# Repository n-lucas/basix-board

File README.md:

# BASIX Board

Open hardware embedded I/O controller for automation and IoT projects.

## Overview

BASIX is an open hardware embedded controller built primarily with through-hole (THT) components and based on the PIC18F46K20 microcontroller, providing Ethernet, RS485 and other peripherals.

It was designed as an educational platform for learning embedded electronics, prototyping automation systems, and experimenting with industrial communication interfaces and isolated I/O.

The complete hardware design is publicly available, including schematics, PCB layouts, manufacturing files, and documentation.

## Features

- 12VDC power input
- PIC18F46K20 microcontroller (16 MHz)
- Ethernet interface (W5500)
- RS-485 interface
- Real-Time Clock (RTC) with backup battery
- External 128 KB SPI EEPROM
- 4× optically isolated digital inputs
- 2× analog inputs (0–10 V)
- 2× relay outputs
- 2× digital/PWM outputs
- 5-position DIP switch for configuration
- 3x General purpose LEDs (feedback, status, etc)
- ICSP programming header

## Fabrication / Assembly

BASIX was designed with simplicity and accessibility in mind. The board uses mostly through-hole (THT) components, allowing it to be assembled using a standard soldering iron without requiring specialized equipment such as a reflow oven or hot-air station.

The PCB can be manufactured by any standard PCB fabrication service using the Gerber files available in the `hardware/gerbers` directory.

This approach makes the project suitable for hobbyists, students, makers, and anyone interested in learning embedded hardware design or building their own automation controller.

## Repository Structure

| Directory | Description |
|---|---|
| `hardware/kicad/` | Editable KiCad project files, including schematics, PCB layout, symbols, and footprints. |
| `hardware/gerbers/` | Gerber and drill files ready for PCB manufacturing. |
| `hardware/bom/` | Bill of Materials (BOM), including component references, quantities, and part numbers. |
| `docs/` | Technical documentation, hardware architecture, schematics, design notes, and revision history. |
| `images/` | Board photographs, KiCad 3D renders, diagrams, and images used throughout the documentation. |

## Documentation

Additional documentation can be found in the `docs` directory.

Topics include:

- Hardware architecture
- Design decisions
- Revision history

## Expansion Modules

BASIX was designed to be easily expanded through its RS-485 interface.

Developers, students, and makers are encouraged to design and share their own expansion modules, such as:

- Remote digital I/O
- Analog input/output modules
- Relay expansion boards
- Environmental sensors
- Energy monitoring
- LCD/HMI interfaces
- Motor controllers
- Industrial protocol gateways

The goal is to build an open ecosystem of interoperable modules that can communicate with BASIX using a simple RS-485 network.

If you develop an expansion board, feel free to share your project with the community by opening a Pull Request or creating your own repository referencing BASIX.

## Project Status

**Current release**

- Hardware Revision C
- Prototype validated

**Planned**

- Open-source firmware
- Desktop application (Lazarus) for monitoring and controlling I/O

## License

This project is licensed under the CERN Open Hardware Licence Version 2 - Weakly Reciprocal (CERN-OHL-W v2).

See the `LICENSE` file for details.

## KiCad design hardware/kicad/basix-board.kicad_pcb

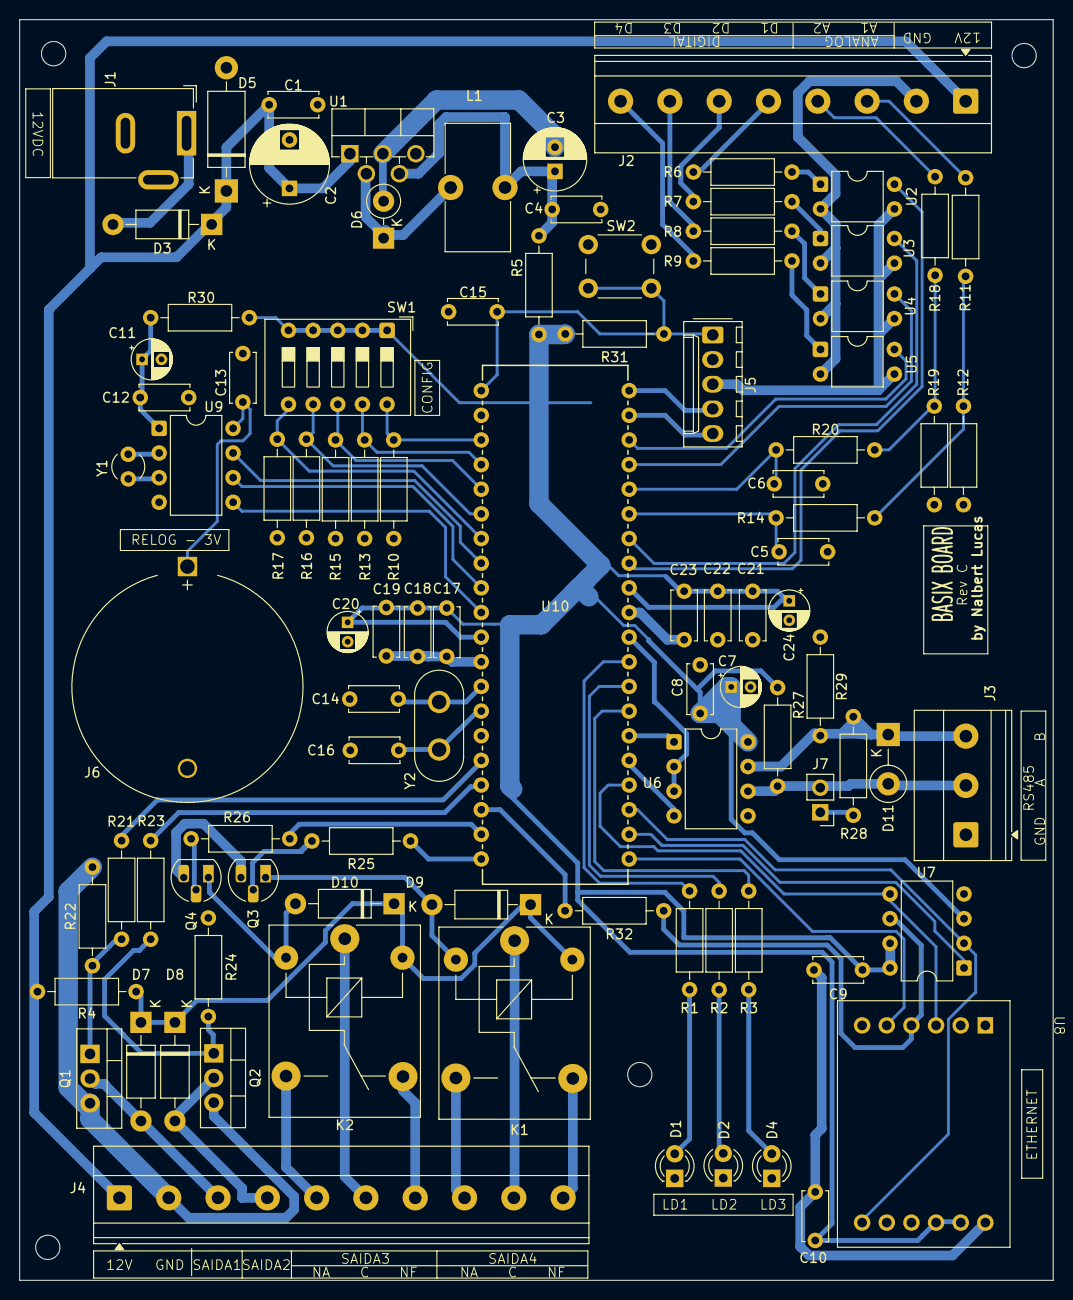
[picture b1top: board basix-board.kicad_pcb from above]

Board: 2 copper layers, 106.5 x 129.9 mm, 95 parts (0 on the bottom side), 78 nets.

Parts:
C1, C4, C5, C6, C8, C9, C10, C12, C13, C14, C15, C16, C17, C18, C19, C21, C22, C23: 100nF; C_Disc_D5.0mm_W2.5mm_P5.00mm
C2: 680uF; CP_Radial_D8.0mm_P5.00mm
C3: 220uF; CP_Radial_D6.3mm_P2.50mm
C7, C11, C20, C24: 10uF; CP_Radial_D4.0mm_P2.00mm
D1, D2, D4: LED; LED_D3.0mm
D3, D7, D8, D9, D10: 1N4007; D_DO-41_SOD81_P10.16mm_Horizontal
D5: P6KE68A; D_DO-15_P12.70mm_Horizontal
D6: 1N5819; D_DO-41_SOD81_P3.81mm_Vertical_KathodeUp
D11: P6KE15CA; D_DO-15_P5.08mm_Vertical_KathodeUp
J1: Barrel Connector; BarrelJack_GCT_DCJ200-10-A_Horizontal
J2: Conn_01x08_Pin; TerminalBlock_Phoenix_MKDS-1,5-8-5.08_1x08_P5.08mm_Horizont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
J3: Conn_01x03_Pin; TerminalBlock_Phoenix_MKDS-1,5-3-5.08_1x03_P5.08mm_Horizont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
J4: Conn_01x10_Pin; TerminalBlock_Phoenix_MKDS-1,5-10-5.08_1x10_P5.08mm_Horizon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
J5: KK Connector; Molex_KK-254_AE-6410-05A_1x05_P2.54mm_Vertical
J6: BAT Connector; BatteryHolder_MYOUNG_BS-07-A1BJ001_CR2032
J7: Conn_01x02_Pin; PinHeader_1x02_P2.54mm_Vertical
K1, K2: SPDT 12V; Relay_SPDT_SANYOU_SRD_Series_Form_C
L1: 33uH; L_Toroid_Vertical_L13.0mm_W6.5mm_P5.60mm
Q1, Q2: IRLZ44N; TO-220-3_Vertical
Q3, Q4: BC548; TO-92_HandSolder
R1, R2, R3: 220R; R_Axial_DIN0207_L6.3mm_D2.5mm_P10.16mm_Horizontal
R4, R5: 0R; R_Axial_DIN0207_L6.3mm_D2.5mm_P10.16mm_Horizontal
R6, R7, R8, R9, R25, R26: 2k2; R_Axial_DIN0207_L6.3mm_D2.5mm_P10.16mm_Horizontal
R10, R12, R13, R15, R16, R17, R19, R31: 10k; R_Axial_DIN0207_L6.3mm_D2.5mm_P10.16mm_Horizontal
R11, R18: 20k; R_Axial_DIN0207_L6.3mm_D2.5mm_P10.16mm_Horizontal
R14, R20: 1k; R_Axial_DIN0207_L6.3mm_D2.5mm_P10.16mm_Horizontal
R21, R23: 100R; R_Axial_DIN0207_L6.3mm_D2.5mm_P10.16mm_Horizontal
R22, R24: 100k; R_Axial_DIN0207_L6.3mm_D2.5mm_P10.16mm_Horizontal
R27, R29: 4k7; R_Axial_DIN0207_L6.3mm_D2.5mm_P10.16mm_Horizontal
R28: 120R; R_Axial_DIN0207_L6.3mm_D2.5mm_P10.16mm_Horizontal
R30: 10R; R_Axial_DIN0207_L6.3mm_D2.5mm_P10.16mm_Horizontal
R32: 33R; R_Axial_DIN0207_L6.3mm_D2.5mm_P10.16mm_Horizontal
SW1: DIP Switch; SW_DIP_SPSTx05_Slide_9.78x14.88mm_W7.62mm_P2.54mm
SW2: SW_Push; SW_PUSH_6mm
U1: LM2596T-3.3; TO-220F-5_P3.4x2.06mm_StaggerEven_Lead1.86mm_Vertical
U2, U3, U4, U5: PC817; DIP-4_W7.62mm
U6: MAX485; DIP-8_W7.62mm
U7: 25LC1024; DIP-8_W7.62mm
U8: W5500 Lite; W5500_Lite_2x6_2.54mm_20.32mm
U9: DS1302+; DIP-8_W7.62mm
U10: pic18f46k20-i/p; PDIP40_600MC_MCH
Y1: Crystal; Crystal_AT310_D3.0mm_L10.0mm_Vertical
Y2: Crystal; Crystal_HC50_Vertical

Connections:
3.3V: C7.1, C8.1, C9.1, C10.1, C17.1, C18.1, C19.1, C20.1, C21.1, C22.1, C23.1, C24.1, J5.2, R5.1, R27.2, R30.1, R31.2, SW1.1, SW1.2, SW1.3, SW1.4, SW1.5, U6.8 (VCC), U7.3 (~WP), U7.7 (~HOLD), U7.8 (VCC), U8.8 (VIN), U8.9 (VIN), U10.11 (VDD), U10.32 (VDD)
12VDC: C1.1, C2.1, D3.1 (K), D5.1 (A1), J2.1, J4.1, R4.1, U1.1 (VIN)
12VDC_IN: D3.2 (A), J1.1
12VDC_OUTs: D7.1 (K), D8.1 (K), D9.1 (K), D10.1 (K), K1.5, K2.5, R4.2
485_A: D11.2 (A2), J3.2, J7.2, R27.1, U6.6 (A)
485_B: D11.1 (A1), J3.3, R28.1, R29.2, U6.7 (B)
485_DE_RE: U6.2 (~RE), U6.3 (DE), U10.30 (RD7)
485_RX: U6.1 (RO), U10.26 (RC7)
485_TX: U6.4 (DI), U10.25 (RC6)
AN_IN1: J2.3, R11.2
AN_IN2: J2.4, R18.2
CS_ETH: U8.5 (CS), U10.21 (RD2)
CS_MEM1: U7.1 (~CS), U10.22 (RD3)
DIG_IN1: J2.5, R6.1
DIG_IN2: J2.6, R7.1
DIG_IN3: J2.7, R8.1
DIG_IN4: J2.8, R9.1
DIP1: R10.1, SW1.10, U10.3 (RA1)
DIP2: R13.1, SW1.9, U10.4 (RA2)
DIP3: R15.1, SW1.8, U10.5 (RA3)
DIP4: R16.1, SW1.7, U10.6 (RA4)
DIP5: R17.1, SW1.6, U10.7 (RA5)
GND: C1.2, C2.2, C3.2, C4.2, C5.2, C6.2, C7.2, C8.2, C9.2, C10.2, C11.2, C12.2, C13.2, C14.2, C15.2, C16.2, C17.2, C18.2, C19.2, C20.2, C21.2, C22.2, C23.2, C24.2, D1.1 (K), D2.1 (K), D4.1 (K), D5.2 (A2), D6.2 (A), J1.2, J2.2, J3.1, J4.2, J5.3, J6.2, Q1.3 (S), Q2.3 (S), Q3.3 (E), Q4.3 (E), R10.2, R12.1, R13.2, R15.2, R16.2, R17.2, R19.1, R22.1, R24.1, R29.1, SW2.1, U1.3 (GND), U1.5 (~ON/OFF), U2.2, U2.3, U3.2, U3.3, U4.2, U4.3, U5.2, U5.3, U6.5 (GND), U7.4 (GND), U8.1 (GND), U8.2 (GND), U8.7 (GND), U9.4 (GND), U10.12 (VSS), U10.31 (VSS)
IN1: U2.4, U10.33 (RB0)
IN2: U3.4, U10.34 (RB1)
IN3: U4.4, U10.37 (RB4)
IN4: U5.4, U10.38 (RB5)
IN5: C5.1, R14.1, U10.35 (RB2)
IN6: C6.1, R20.1, U10.36 (RB3)
LED1: R1.2, U10.29 (RD6)
LED2: R2.2, U10.28 (RD5)
LED3: R3.2, U10.27 (RD4)
LOAD1: D7.2 (A), J4.3, Q1.2 (D)
LOAD2: D8.2 (A), J4.4, Q2.2 (D)
LOAD3_C: J4.6, K2.1
LOAD3_NA: J4.5, K2.3
LOAD3_NF: J4.7, K2.4
LOAD4_C: J4.9, K1.1
LOAD4_NA: J4.8, K1.3
LOAD4_NF: J4.10, K1.4
MCLR: C15.1, J5.1, R31.1, SW2.2, U10.1 (MCLR*/VPP/RE3)
MISO: U7.2 (MISO), U8.12 (MISO), U10.23 (RC4)
MOSI: U7.5 (MOSI), U8.3 (MOSI), U10.24 (RC5)
unnamed: D1.2 (A), R1.1
unnamed: D2.2 (A), R2.1
unnamed: D4.2 (A), R3.1
unnamed: D6.1 (K), L1.1, U1.2 (OUT)
unnamed: D9.2 (A), K1.2, Q3.1 (C)
unnamed: D10.2 (A), K2.2, Q4.1 (C)
unnamed: J7.1, R28.2
unnamed: Q1.1 (G), R21.2, R22.2
unnamed: Q2.1 (G), R23.2, R24.2
unnamed: Q3.2 (B), R25.2
unnamed: Q4.2 (B), R26.2
unnamed: R6.2, U2.1
unnamed: R7.2, U3.1
unnamed: R8.2, U4.1
unnamed: R9.2, U5.1
unnamed: R11.1, R12.2, R14.2
unnamed: R18.1, R19.2, R20.2
unnamed: C3.1, C4.1, L1.2, R5.2, U1.4 (FB)
unnamed: C11.1, C12.1, R30.2, U9.1 (VCC2)
unnamed: U9.2 (X1), Y1.1
unnamed: U9.3 (X2), Y1.2
unnamed: R32.1, U10.18 (RC3)
OUT1: R21.1, U10.16 (RC1)
OUT2: R23.1, U10.17 (RC2)
OUT3: R26.1, U10.19 (RD0)
OUT4: R25.1, U10.20 (RD1)
PGC: J5.5, U10.39 (RB6)
PGD: J5.4, U10.40 (RB7)
RTC_BAT: C13.1, J6.1, U9.8 (VCC1)
RTC_CE: U9.5 (CE), U10.10 (RE2)
RTC_CLK: U9.7 (SCLK), U10.8 (RE0)
RTC_DAT: U9.6 (I/O), U10.9 (RE1)
SCLK: R32.2, U7.6 (SCK), U8.4 (SCLK)
X1: C14.1, U10.13 (RA7), Y2.1
X2: C16.1, U10.14 (RA6), Y2.2
